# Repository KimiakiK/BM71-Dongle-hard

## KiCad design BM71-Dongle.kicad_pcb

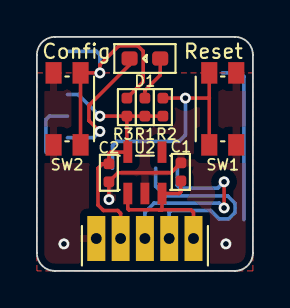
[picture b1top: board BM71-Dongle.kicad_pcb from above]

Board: 2 copper layers, 12.0 x 13.0 mm, 11 parts (1 on the bottom side), 9 nets.

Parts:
C1, C2: 1uF; 1005Metric
D1: LED; 1608Metric
J1: USB_B_Micro; USB MicroB Male
R1: R; 1005Metric
R2, R3: 4k7; 1005Metric
SW1, SW2: SW; SideSW_THAF01-NC-R
U1: BM71
U2: NJM12877F33; SOT-23-5

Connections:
+3.3V: C2.1, J1.4 (ID), R1.2, R2.1, R3.1, U1.14 (VBAT), U2.5 (VOUT)
+5V: C1.1, J1.1 (VBUS), U2.1 (VIN), U2.3 (CTRL)
BM71_RXD: J1.3 (D+), U1.7 (HCI_RXD)
BM71_TXD: J1.2 (D-), U1.8 (HCI_TXD)
CONFIG: R3.2, SW2.1, U1.16 (P2_0)
GND: C1.2, C2.2, J1.5 (GND), SW1.2, SW2.2, U1.2 (GND), U1.13 (GND), U2.2 (GND)
LED: D1.1 (K), U1.12 (P0_2)
unnamed: D1.2 (A), R1.1
RESET: R2.2, SW1.1, U1.10 (RST_N)

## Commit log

2022-11-13 基板V1.0
2023-01-08 基板 V2.0
